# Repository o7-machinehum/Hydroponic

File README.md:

# The Robotanist 
The Robotanist is a fully integrated and automated hydroponic rig. 

Electronics

Please find the electronics files in the ee folder, all pcb design is done with
the open source software KiCad. Is uses an STM32 as the main controller, and an
ST L6470 moter driver for the stepper motor. There are various connectors for
the subsystem components.

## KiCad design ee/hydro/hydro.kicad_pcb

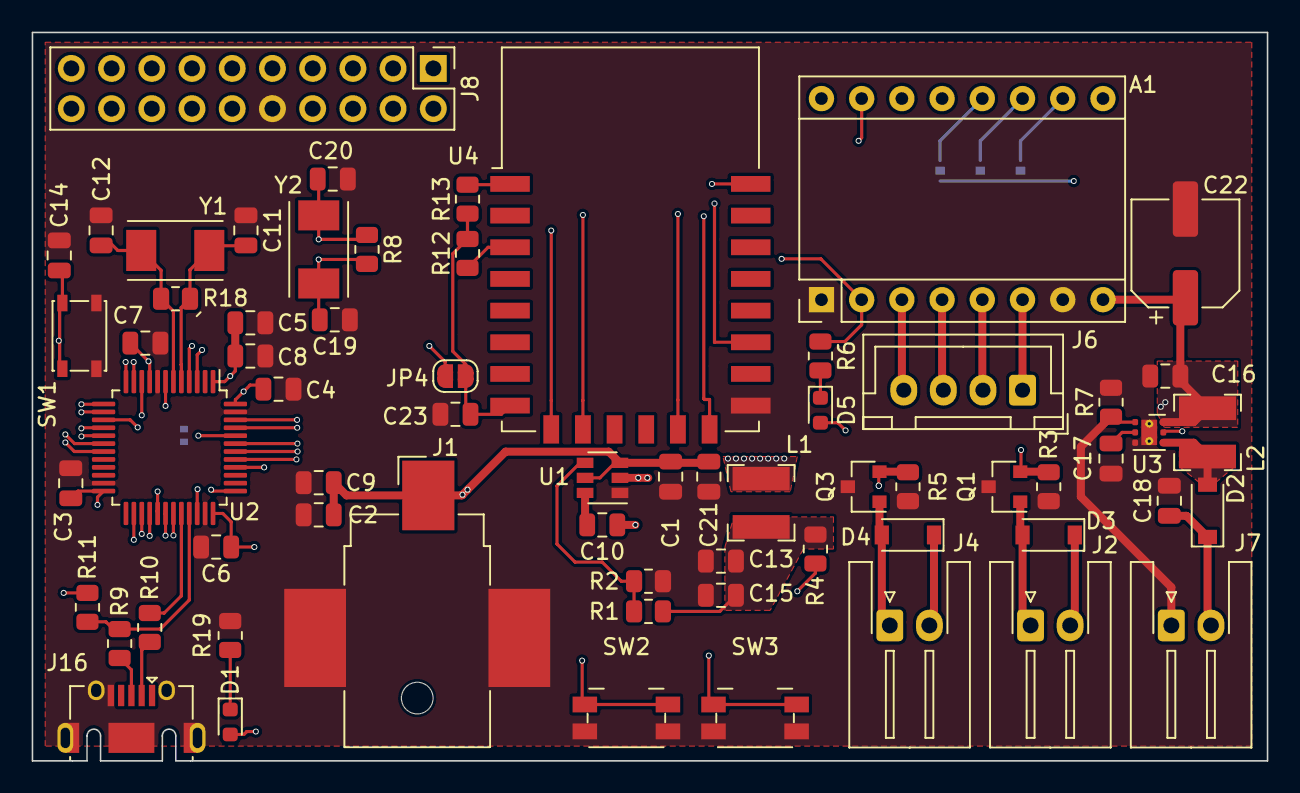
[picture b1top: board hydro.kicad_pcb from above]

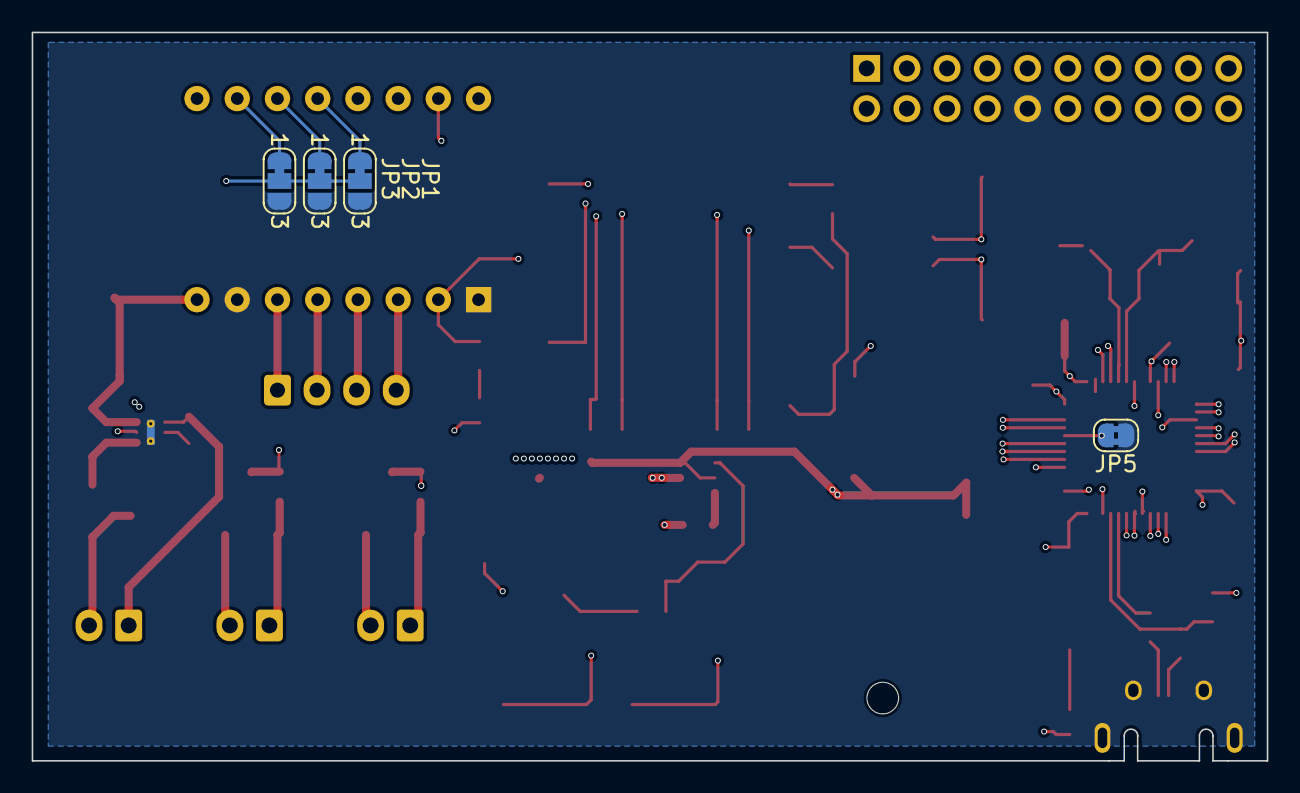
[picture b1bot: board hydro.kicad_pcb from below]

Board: 4 copper layers, 78.0 x 46.0 mm, 69 parts (4 on the bottom side), 65 nets.

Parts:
A1: DRV8825; Pololu_Breakout-16_15.2x20.3mm
C1, C13, C15: 22uF; C_0805_2012Metric
C2, C3, C9, C10: 10uF; C_0805_2012Metric
C4, C5, C6, C7, C8: 0.1uF; C_0805_2012Metric
C11, C12, C19, C20: 20pF; C_0805_2012Metric
C14, C16, C18, C21, C23: 1uF; C_0805_2012Metric
C17: 220nF; C_0805_2012Metric
C22: 100uF; CP_Elec_6.3x5.4
D1: LED Green; LED_0603_1608Metric
D2, D3, D4: MBR0540; D_SOD-123
D5: LED Red; LED_0603_1608Metric
J1: PJ-036AH-SMT-TR; BarrelJack_CUI_PJ-036AH-SMT_Horizontal
J2, J4, J7: Conn_01x02_Male; JST_XH_S2B-XH-A-1_1x02_P2.50mm_Horizontal
J6: Conn_01x04_Male; JST_XH_B4B-XH-A_1x04_P2.50mm_Vertical
J8: Conn_02x10_Counter_Clockwise; PinHeader_2x10_P2.54mm_Vertical
J16: USB_B_Micro; USB_Micro-AB_Molex_47590-0001
JP1, JP2, JP3: SolderJumper_3_Bridged12; SolderJumper-3_P1.3mm_Bridged12_RoundedPad1.0x1.5mm_NumberL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
JP4: Jumper_2_Open; SolderJumper-2_P1.3mm_Open_RoundedPad1.0x1.5mm
JP5: Jumper_2_Bridged; SolderJumper-2_P1.3mm_Bridged2Bar_RoundedPad1.0x1.5mm
L1: 3.3uH; L_Bourns-SRN4018
L2: 22uH; L_Bourns-SRN4018
Q1, Q3: DMP3099L-13; SOT-23
R1: 33.2k; R_0805_2012Metric
R2, R3, R5: 10k; R_0805_2012Metric
R4: 0R; R_0805_2012Metric
R6, R19: 1k; R_0805_2012Metric
R7: 10R; R_0805_2012Metric
R8, R12, R13, R18: 1M; R_0805_2012Metric
R9, R10: 20R; R_0805_2012Metric
R11: 1.5k; R_0805_2012Metric
SW1: Reset; SW_SPST_PTS810
SW2: Drain Tank; Panasonic_EVQPUJ_EVQPUA
SW3: Fill Tank; Panasonic_EVQPUJ_EVQPUA
U1: TPS562200DDCR; SOT-23-6
U2: STM32F103C8Tx; LQFP-48_7x7mm_P0.5mm
U3: TPS61161; WSON-6-1EP_2x2mm_P0.65mm_EP1x1.6mm_ThermalVias
U4: ESP-12E
Y1: 8Mhz; Crystal_SMD_Abracon_ABM7-2Pin_6.0x3.5mm
Y2: 32.768Khz; Crystal_SMD_Abracon_ABM7-2Pin_6.0x3.5mm

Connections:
+3V3: C3.1, C4.1, C5.1, C6.1, C7.1, C8.1, D5.2, J8.1, JP1.2, JP2.2, JP3.2, JP4.1, R4.2, R11.1, U2.1, U2.9, U2.24, U2.36, U2.48
+12V: A1.8, C1.1, C2.1, C9.1, C16.1, C21.1, C22.1, D3.1, D4.1, J1.1, J2.2, J4.2, L2.1, U1.3, U1.5, U3.6
/!RST: C14.1, SW1.1, U2.7
/Connector/LED_FB: J7.1, R7.1, U3.1
/Connector/LED_OUT: C18.1, D2.1, J7.2
/Connector/Mot_M0: A1.10, JP3.1
/Connector/Mot_M1: A1.11, JP2.1
/Connector/Mot_M2: A1.12, JP1.1
/Drain: SW2.1, U2.27
/ESP_CS0: J8.9, U4.9
/ESP_MISO: J8.8, U4.10
/ESP_MOSI: J8.7, U4.13
/ESP_RX: J8.5, U4.17
/ESP_SCLK: J8.6, U4.14
/ESP_TX: J8.4, U4.22
/Fill: SW3.1, U2.28
/LED: D1.2, U2.26
/Mot_Dir: A1.2, R6.1, U2.41
/Mot_En: A1.9, U2.40
/PA1: J8.14, U2.11
/PA2: J8.13, U2.12
/PA3: J8.16, U2.13
/PA4: J8.15, U2.14
/PA6: J8.18, U2.16
/PA7: J8.17, U2.17
/PB0: J8.19, U2.18
/PB1: J8.20, U2.19
/PB7: A1.13, U2.43
/PB8: A1.14, U2.45
/PB9: A1.16, U2.46
/Power/SW: C10.1, L1.2, U1.2
/Power/VBST: C10.2, U1.6
/Power/VFB: R1.2, R2.1, U1.4
/SWDCLK: J8.3, U2.37
/SWDIO: J8.2, U2.34
/TIM1_Pump1: Q1.2, R3.1, U2.10
/TIM2_LED: U2.29, U3.5
/TIM3_Pump2: Q3.2, R5.1, U2.15
/TIM4_Step: A1.15, U2.42
/UART1_RX: J8.11, U2.31
/UART1_TX: J8.12, U2.30
/USB_DM: R10.2, U2.32
/USB_DP: R9.2, R11.2, U2.33
GND: A1.1, A1.7, C1.2, C2.2, C3.2, C4.2, C5.2, C6.2, C7.2, C8.2, C9.2, C11.1, C12.1, C13.2, C14.2, C15.2, C16.2, C17.2, C18.2, C19.1, C20.1, C21.2, C22.2, C23.2, J1.2, J1.3, J8.10, J16.5, J16.6, JP1.3, JP2.3, JP3.3, JP5.1, Q1.3, Q3.3, R2.2, R3.2, R5.2, R7.2, R19.1, SW1.2, SW2.2, SW3.2, U1.1, U2.8, U2.23, U2.35, U2.47, U3.3, U3.7, U4.15
LF_OSC_IN: C19.2, R8.2, U2.3, Y2.1
LF_OSC_OUT: C20.2, R8.1, U2.4, Y2.2
unnamed: A1.3, J6.4
unnamed: A1.4, J6.3
unnamed: A1.5, J6.2
unnamed: A1.6, J6.1
unnamed: C13.1, C15.1, L1.1, R1.1, R4.1
unnamed: C17.1, U3.2
unnamed: D1.1, R19.2
unnamed: D2.2, L2.2, U3.4
unnamed: D3.2, J2.1, Q1.1
unnamed: D4.2, J4.1, Q3.1
unnamed: D5.1, R6.2
unnamed: J16.2, R10.1
unnamed: J16.3, R9.1
unnamed: JP5.2, U2.44
unnamed: R12.1, U4.3
unnamed: R13.1, U4.1
OSC_IN: C11.2, R18.2, U2.5, Y1.1
OSC_OUT: C12.2, R18.1, U2.6, Y1.2
VPP: C23.1, JP4.2, R12.2, R13.2, U4.8

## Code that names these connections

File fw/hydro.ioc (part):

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PC15-OSC32_OUT.Mode=LSE-External-Oscillator
PD1-OSC_OUT.Mode=HSE-External-Oscillator
Mcu.UserName=STM32F103C8Tx
PC13-TAMPER-RTC.Signal=GPIO_Output
PA11.Mode=Device
PD0-OSC_IN.Signal=RCC_OSC_IN
PC14-OSC32_IN.Signal=RCC_OSC32_IN
RCC.SYSCLKSource=RCC_SYSCLKSOURCE_PLLCLK
PD1-OSC_OUT.Signal=RCC_OSC_OUT
PA13.Signal=SYS_JTMS-SWDIO
PA12.Signal=USB_DP
PC15-OSC32_OUT.Signal=RCC_OSC32_OUT
PD0-OSC_IN.Mode=HSE-External-Oscillator
board=custom
PC14-OSC32_IN.Mode=LSE-External-Oscillator
PA14.Mode=Serial_Wire
PA13.Mode=Serial_Wire
Mcu.Name=STM32F103C(8-B)Tx
RCC.SYSCLKFreq_VALUE=48000000
Mcu.Package=LQFP48
PA12.Mode=Device
PA11.Signal=USB_DM
PA14.Signal=SYS_JTCK-SWCLK

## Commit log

2020-11-09 Initial commit. All parts fine with FreeCAD 0.18
2020-11-16 Added all the parts
2020-11-23 Mech is looking good, added some supply documents and emails.
2020-11-25 Working away on the mech. Split the main assembly into two pieces
2020-11-25 Left some parts behind
2020-11-25 Initial firmware commit
2020-11-26 Generate some new parts. Couple of changed in the assembly.
2020-11-28 Working on the mech, changed some hole sizes
2020-12-03 Huge overhaul
2020-12-03 Removed submodule
2020-12-03 Ripped out the cube shit, going with libopencm3
2020-12-04 Building with errors
2020-12-04 Seperated the CPP flags and the C flags
2020-12-07 Uart plummed into the CLI
2020-12-08 Cleaned up the warnings, cli working nicely
2020-12-09 Added readme, added pump clamps
2020-12-11 Added pump stl files and gcode.
2020-12-11 Buffed out all the warnings
2020-12-11 pwm classes built, need to clean up the warnings
2020-12-11 Wrote up a little readme
2020-12-11 plx don't use the -Wshadow flag
2020-12-11 Implemented period and duc in the class
2020-12-11 PWM freq & DUC working fine
2020-12-11 Moved the clock start outta the pwm class
2020-12-15 Worked on the cli. The cli object now holds menu rather than you having to pass it into the present() function. Backspaces now work on the cli
2020-12-15 Help command almost working
2020-12-16 Worked on the command mode
2020-12-16 Added some stuff to the readme
2020-12-23 Working on the PCB
2020-12-23 Working on the mech
2020-12-23 Added the color sensor
2020-12-24 Working on the board, parts are in place. Need som mounting holes.
2020-12-29 Unknown changes
2020-12-29 Added annoying files to the gitignore
2020-12-29 Working on the readme
2021-01-02 Working on the ee parts of the design, placed two switches for fill and drain. Moved around some parts.
2021-01-07 Routing out the pins for the MCU
2021-01-07 Working on the board
2021-01-11 Routing "finished", building a master todo list now.
